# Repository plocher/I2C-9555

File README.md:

# I2C-9555
## License: CERN Open Hardware Licence v1.2

A compliment to the [I2C-8574](/pages/I2C-8574.html) dual 8-bit board, the 9555 offers a 16 bit data path (2x 8-bit ports, port0 and port1)
This board is slightly cheaper to build (1x 9555 chip -vs- 2x 8574 chips...), but slightly harder to use (unpacking 16 bit words into byte size chunks)

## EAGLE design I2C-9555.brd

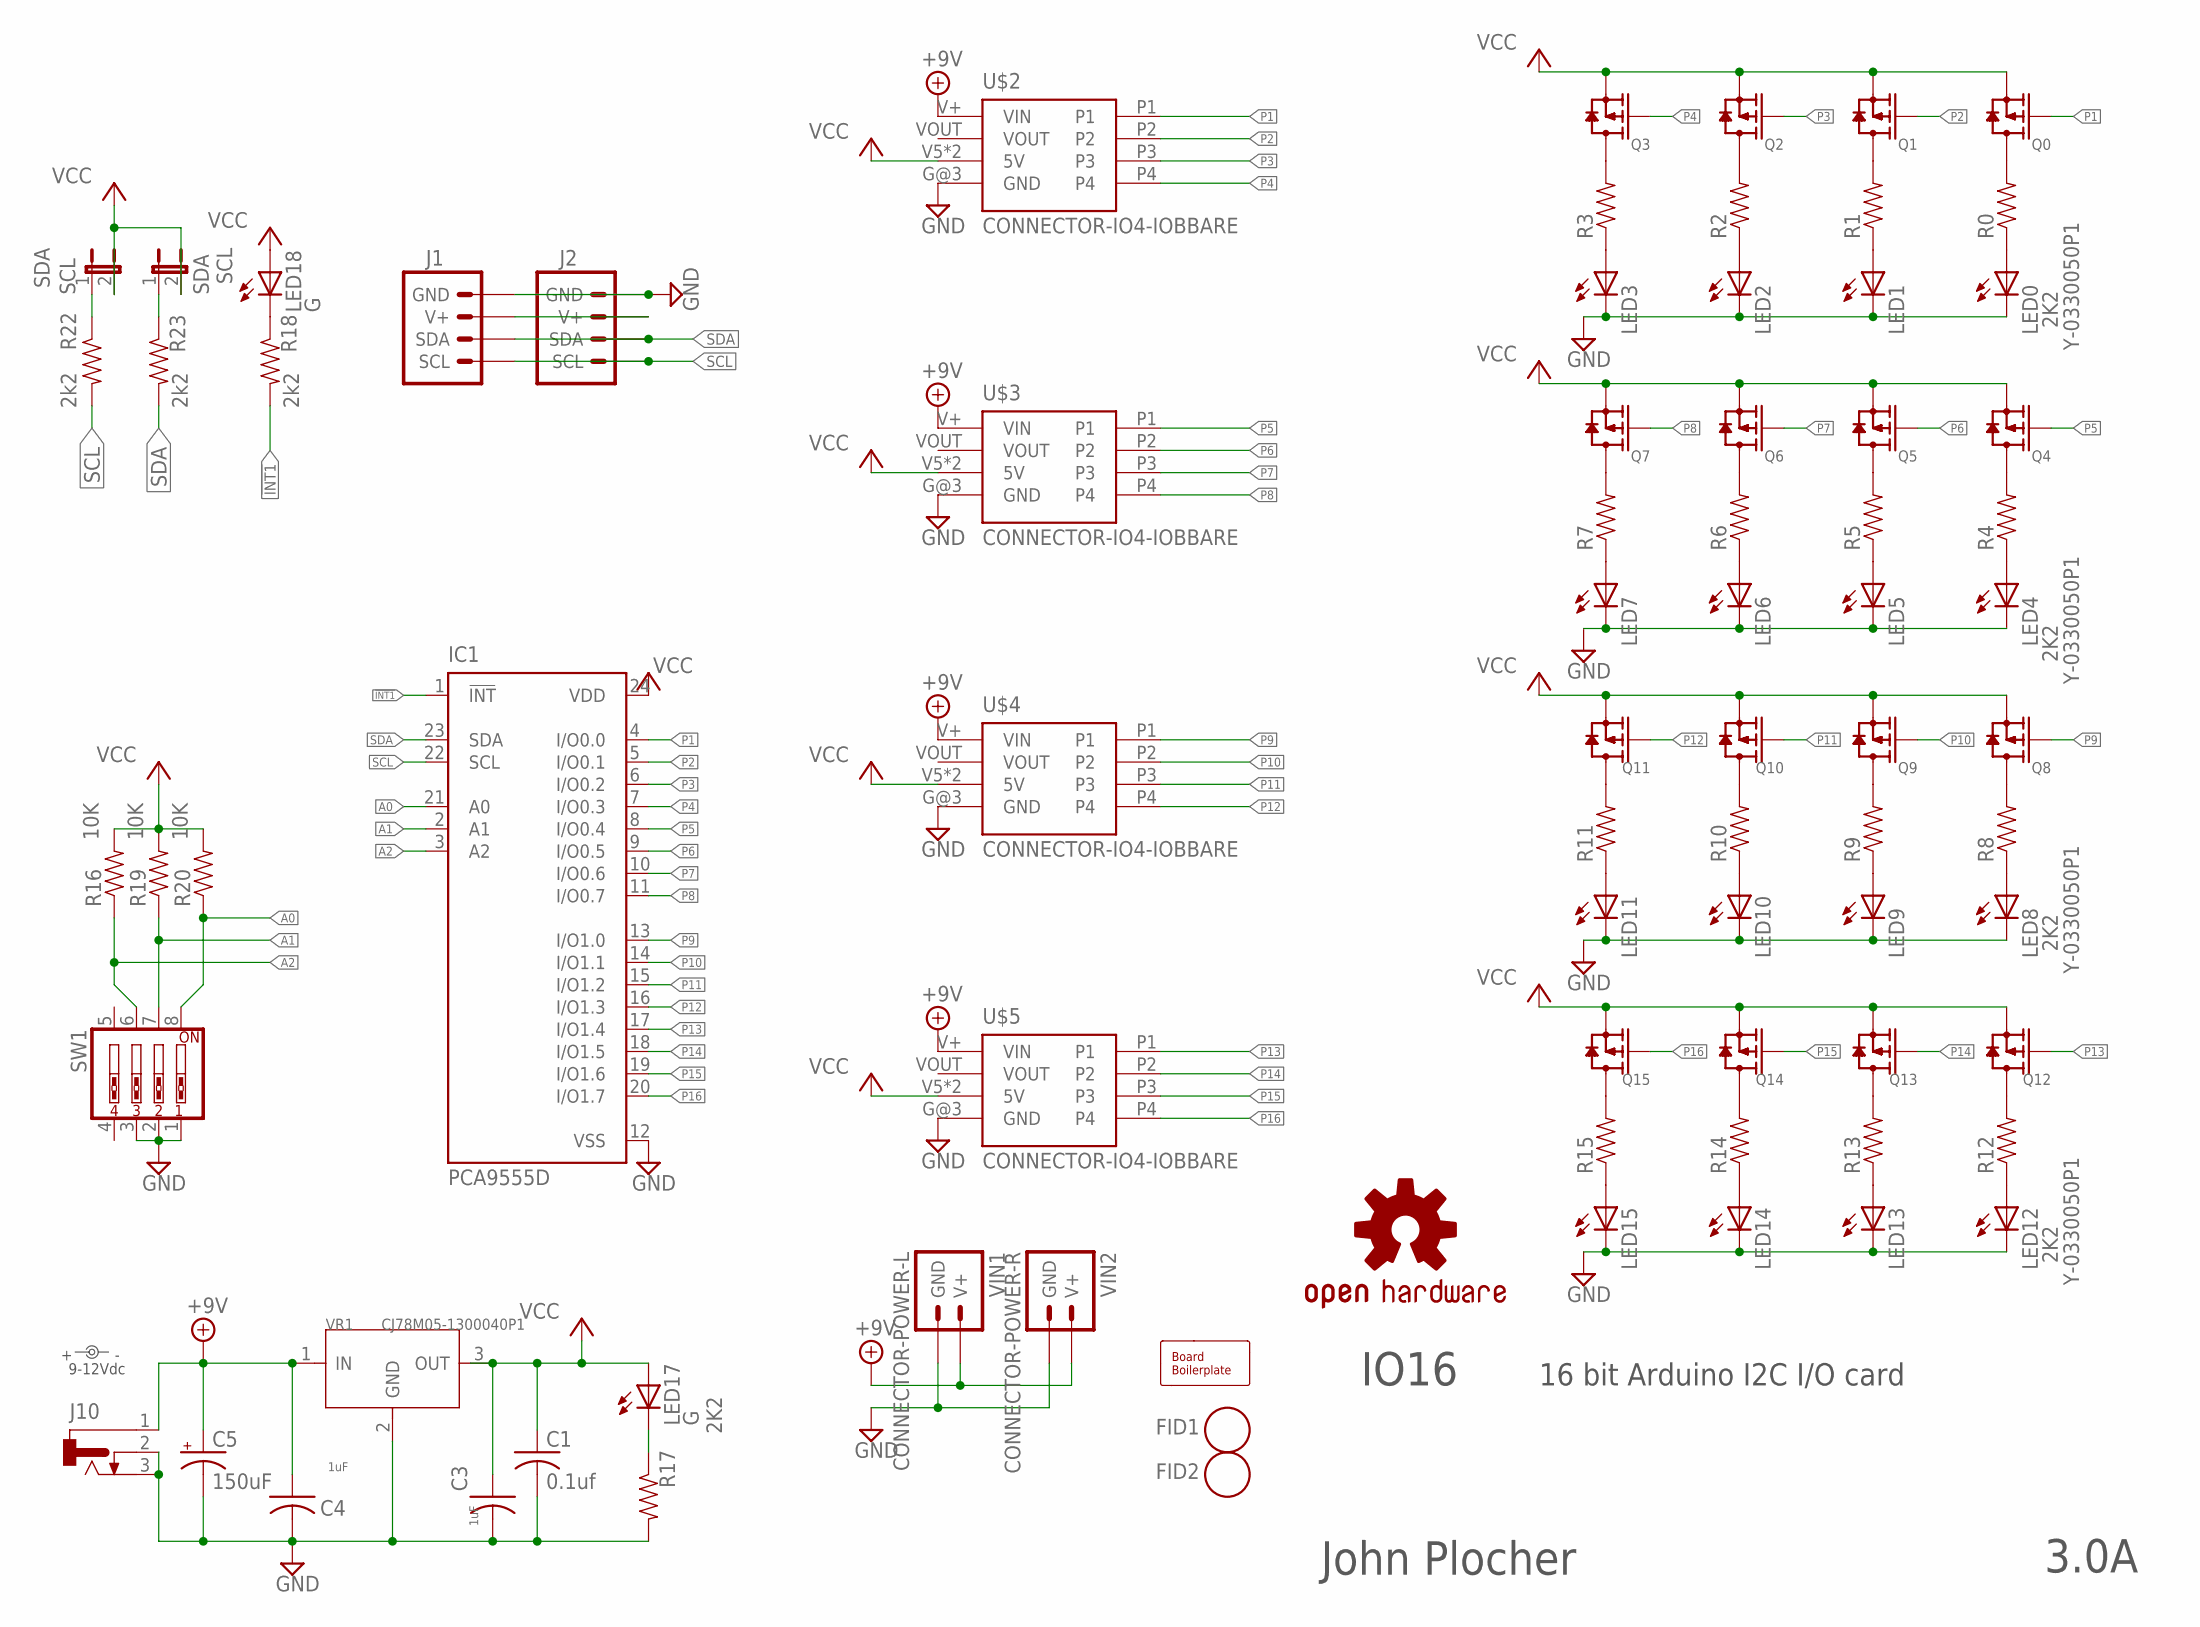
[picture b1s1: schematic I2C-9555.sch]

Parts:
BOARD1: BOARD80X100-IOB; BOARD-DINRAIL-3.17IN-IOB
C1: 0.1uf; 0805-CAP
C3, C4: 1uF; 0805-CAP
C5: 150uF; 0810-CAP
FID1, FID2: FIDUCIAL; FIDUCIAL_1MM
IC1: PCA9555D; SO24
J1, J2: CONNECTOR-I2CLEFT; I2C-L
J10: CONNECTOR-DC-POWER-RA; DCJ0202
LED0, LED1, LED2, LED3, LED4, LED5, LED6, LED7, LED8, LED9, LED10, LED11, LED12, LED13, LED14, LED15: Y-0330050P1; 0603-LED
LED17, LED18: G; 0603-LED
POWER: 9-12Vdc; PWR_LABEL
Q0, Q1, Q2, Q3, Q4, Q5, Q6, Q7, Q8, Q9, Q10, Q11, Q12, Q13, Q14, Q15: MOSFET-P; SOT23-3
R0, R1, R2, R3, R4, R5, R6, R7, R8, R9, R10, R11, R12, R13, R14, R15, R17: 2K2; 0805-RES
R16, R19, R20: 10K; 0805-RES
R18, R22, R23: 2k2; 0805-RES
SCL: SDA; 1X02_LOCK
SDA: SCL; 1X02_LOCK
SW1: SW_DIP-4; EDG-04
U$1: OSHW-LOGOL; OSHW-LOGO-L
U$2, U$3, U$4, U$5: CONNECTOR-IO4-IOBBARE; IO4-IOB
VIN1: CONNECTOR-POWER-L; POWER-R2
VIN2: CONNECTOR-POWER-R; POWER-R
VR1: CJ78M05-1300040P1; TO252

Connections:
!INT1: IC1.1 (!INT), R18.2
+9V: C4.1, C5.+, J10.1, U$2.V+ (VIN), U$3.V+ (VIN), U$4.V+ (VIN), U$5.V+ (VIN), VIN1.V+, VIN1.V+@1 (V+), VIN1.V+@2 (V+), VIN1.V+@3 (V+), VIN2.V+, VIN2.V+@1 (V+), VIN2.V+@2 (V+), VIN2.V+@3 (V+), VR1.1 (IN)
A0: IC1.21 (A0), R20.1, SW1.8
A1: IC1.2 (A1), R19.1, SW1.7
A2: IC1.3 (A2), R16.1, SW1.6
GND: C1.2, C3.2, C4.2, C5.-, IC1.12 (VSS), J1.GND, J1.GND@1 (GND), J2.GND, J2.GND@1 (GND), J10.2, J10.3, LED0.C, LED1.C, LED2.C, LED3.C, LED4.C, LED5.C, LED6.C, LED7.C, LED8.C, LED9.C, LED10.C, LED11.C, LED12.C, LED13.C, LED14.C, LED15.C, R17.2, SW1.1, SW1.2, SW1.3, U$2.G@3 (GND), U$3.G@3 (GND), U$4.G@3 (GND), U$5.G@3 (GND), VIN1.GND, VIN1.GND@1 (GND), VIN1.GND@2 (GND), VIN1.GND@3 (GND), VIN2.GND, VIN2.GND@1 (GND), VIN2.GND@2 (GND), VIN2.GND@3 (GND), VR1.2 (GND)
unnamed: LED17.C, R17.1
unnamed: LED3.A, R3.1
unnamed: LED2.A, R2.1
unnamed: LED1.A, R1.1
unnamed: LED0.A, R0.1
unnamed: LED4.A, R4.1
unnamed: LED5.A, R5.1
unnamed: Q4.3 (D), R4.2
unnamed: LED6.A, R6.1
unnamed: LED7.A, R7.1
unnamed: Q0.3 (D), R0.2
unnamed: Q5.3 (D), R5.2
unnamed: Q6.3 (D), R6.2
unnamed: Q7.3 (D), R7.2
unnamed: LED11.A, R11.1
unnamed: LED10.A, R10.1
unnamed: LED9.A, R9.1
unnamed: Q8.3 (D), R8.2
unnamed: R23.1, SCL.1
unnamed: R22.1, SDA.1
unnamed: LED8.A, R8.1
unnamed: Q9.3 (D), R9.2
unnamed: Q10.3 (D), R10.2
unnamed: Q11.3 (D), R11.2
unnamed: LED15.A, R15.1
unnamed: LED14.A, R14.1
unnamed: LED13.A, R13.1
unnamed: LED12.A, R12.1
unnamed: Q1.3 (D), R1.2
unnamed: Q2.3 (D), R2.2
unnamed: Q3.3 (D), R3.2
unnamed: Q12.3 (D), R12.2
unnamed: Q13.3 (D), R13.2
unnamed: Q14.3 (D), R14.2
unnamed: Q15.3 (D), R15.2
unnamed: LED18.C, R18.1
unnamed: J1.V+, J1.V+@1 (V+), J2.V+, J2.V+@1 (V+)
P1: IC1.4 (I/O0.0), Q0.1 (G), U$2.P1
P2: IC1.5 (I/O0.1), Q1.1 (G), U$2.P2
P3: IC1.6 (I/O0.2), Q2.1 (G), U$2.P3
P4: IC1.7 (I/O0.3), Q3.1 (G), U$2.P4
P5: IC1.8 (I/O0.4), Q4.1 (G), U$3.P1
P6: IC1.9 (I/O0.5), Q5.1 (G), U$3.P2
P7: IC1.10 (I/O0.6), Q6.1 (G), U$3.P3
P8: IC1.11 (I/O0.7), Q7.1 (G), U$3.P4
P9: IC1.13 (I/O1.0), Q8.1 (G), U$4.P1
P10: IC1.14 (I/O1.1), Q9.1 (G), U$4.P2
P11: IC1.15 (I/O1.2), Q10.1 (G), U$4.P3
P12: IC1.16 (I/O1.3), Q11.1 (G), U$4.P4
P13: IC1.17 (I/O1.4), Q12.1 (G), U$5.P1
P14: IC1.18 (I/O1.5), Q13.1 (G), U$5.P2
P15: IC1.19 (I/O1.6), Q14.1 (G), U$5.P3
P16: IC1.20 (I/O1.7), Q15.1 (G), U$5.P4
SCL: IC1.22 (SCL), J1.SCL, J1.SCL@1 (SCL), J2.SCL, J2.SCL@1 (SCL), R22.2
SDA: IC1.23 (SDA), J1.SDA, J1.SDA@1 (SDA), J2.SDA, J2.SDA@1 (SDA), R23.2
VCC: C1.1, C3.1, IC1.24 (VDD), LED17.A, LED18.A, Q0.2 (S), Q1.2 (S), Q2.2 (S), Q3.2 (S), Q4.2 (S), Q5.2 (S), Q6.2 (S), Q7.2 (S), Q8.2 (S), Q9.2 (S), Q10.2 (S), Q11.2 (S), Q12.2 (S), Q13.2 (S), Q14.2 (S), Q15.2 (S), R16.2, R19.2, R20.2, SCL.2, SDA.2, U$2.V5 (5V), U$2.V5@1 (5V), U$3.V5 (5V), U$3.V5@1 (5V), U$4.V5 (5V), U$4.V5@1 (5V), U$5.V5 (5V), U$5.V5@1 (5V), VR1.3 (OUT)

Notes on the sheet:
IO16
16 bit Arduino I2C I/O card
John Plocher
3.0A

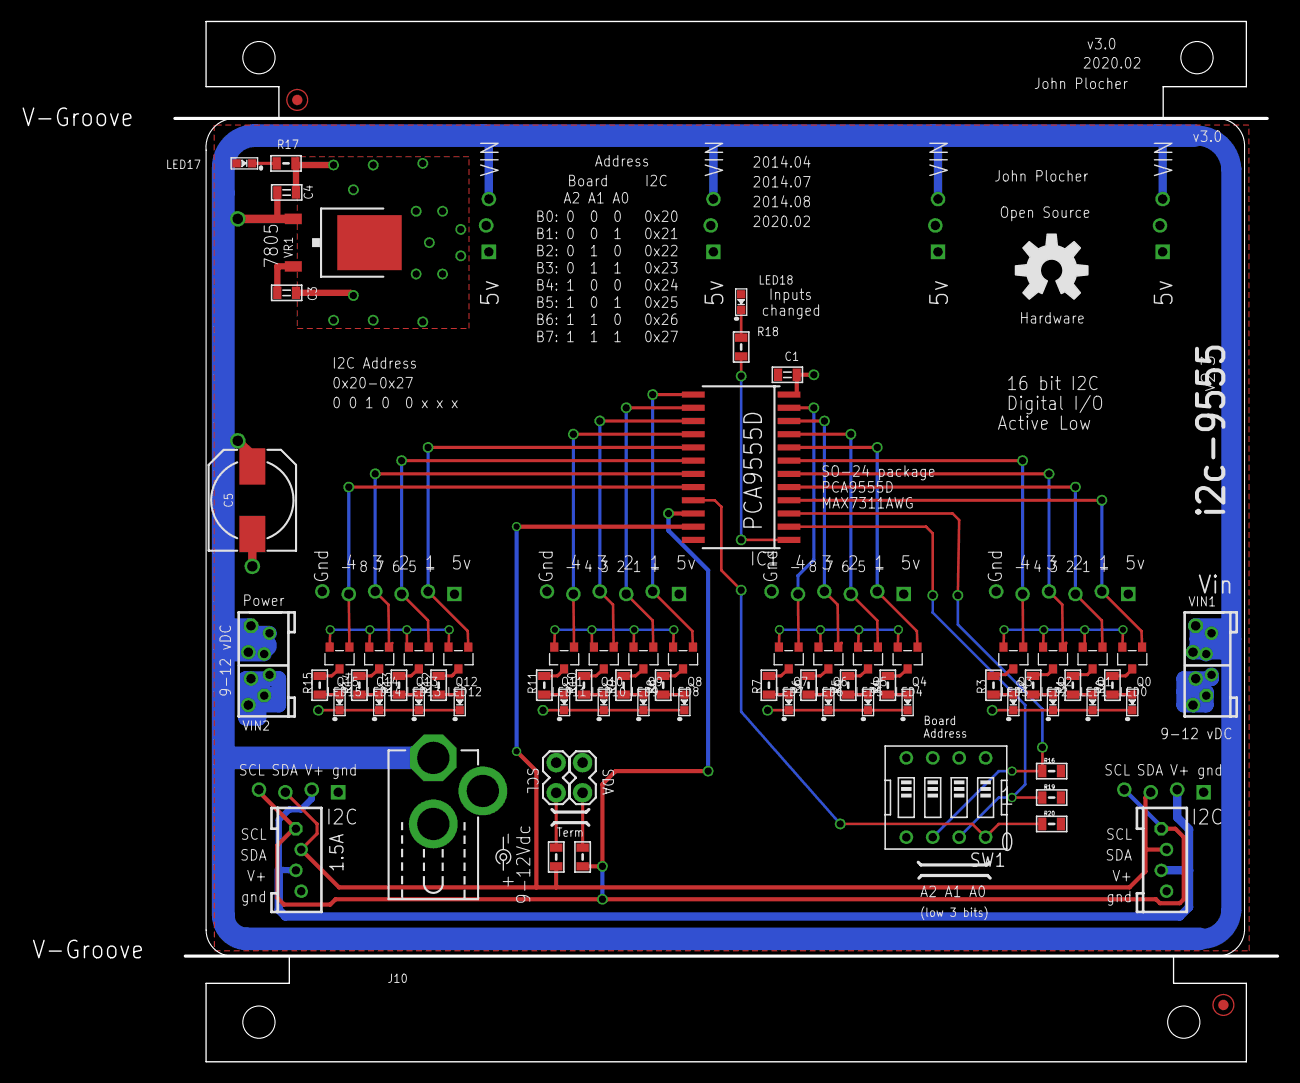
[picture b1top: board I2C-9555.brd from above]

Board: 2 copper layers, 120.7 x 99.8 mm, 80 parts (0 on the bottom side), 62 nets.

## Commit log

2020-03-07 new IOB and power connectors
2020-05-04 updated tags
